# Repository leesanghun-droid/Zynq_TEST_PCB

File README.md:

Open kakao talk [LINK](https://open.kakao.com/o/gl8sklo)
# Zynq_TEST_PCB

Tool : kicad 6.0

  MAIN CHIP : XC7Z010-1CLG400C ([buy link](https://ko.aliexpress.com/item/4000052820744.html?gatewayAdapt=glo2kor&spm=a2g0o.order_list.0.0.21ef140fnMWK8L),  [metal mask buy link](https://ko.aliexpress.com/item/1005003821741873.html?gatewayAdapt=glo2kor&spm=a2g0o.order_list.0.0.21ef140fnMWK8L))

  DDR RAM CHIP : MT41K256M16HA-125( just usb form factor )

## Project step

### 1. make concept ( ~ 2022.04.05 )

      - 100Mbps ethernet
      - usb 2.0
      - ddr3 256MB 667Mhz
      - sd_card
      
### 2. drawing schematic ( ~ 2022.04.20 )

MAIN : XC7Z010-1CLG400C
POWER : ADP5052
JTAG : FT2232HQ
FLASH memory : 

4GB eMMC Flash
16MB QSPI Flash
TF card interface

DRAM : micron 4KK77-D9PTK
512MB DDR3 SDRAM (2 x 256MB, 32-bit)

DDR 고속 배선 아트웍 참조
https://m.blog.naver.com/PostView.naver?isHttpsRedirect=true&blogId=bestmind4276&logNo=220702125147

ethernet : RTL8211E
10/100/1000M Ethernet

usb host : USB3320C

아트웍 순서

1. DDR
2. EMMC
3. ETHERNET
4. USB
5. JTAG 
6. POWER

### 3. order pcb 

      - 4layer ( or 6layer )
      
### 4. hand Soldering

      - usb Metal Mask ( PCB Stencil )
      - HOT AIR FLOW GUN
      - FREE HEATTING BED
      
### 5. standard alone program test

### 6. linux poting

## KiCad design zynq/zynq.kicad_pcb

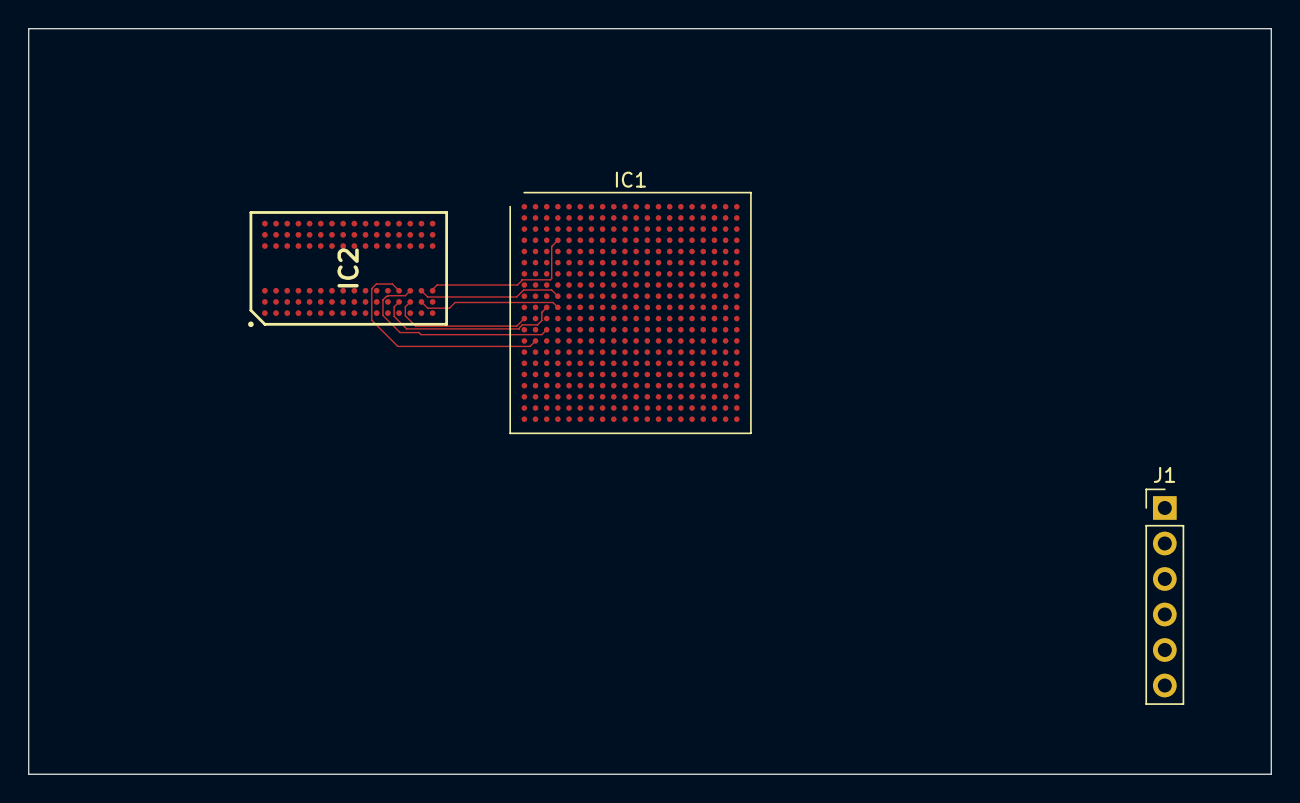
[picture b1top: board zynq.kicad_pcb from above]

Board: 6 copper layers, 88.9 x 53.3 mm, 3 parts (0 on the bottom side), 37 nets.

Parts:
IC1: Xilinx_CLG400
IC2: MT41J128M16JT-125_K; BGA96C80P9X16_800X1400X120
J1: POWER_SOURCE; PinHeader_1x06_P2.54mm_Vertical

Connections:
/CPU/DDR3_A0: IC1.N2 (PS_DDR_A0_502), IC2.N3 (A0)
/CPU/DDR3_A1: IC1.K2 (PS_DDR_A1_502), IC2.P7 (A1)
/CPU/DDR3_A2: IC1.M3 (PS_DDR_A2_502), IC2.P3 (A2)
/CPU/DDR3_A3: IC1.K3 (PS_DDR_A3_502), IC2.N2 (A3)
/CPU/DDR3_A4: IC1.M4 (PS_DDR_A4_502), IC2.P8 (A4)
/CPU/DDR3_A5: IC1.L1 (PS_DDR_A5_502), IC2.P2 (A5)
/CPU/DDR3_A6: IC1.L4 (PS_DDR_A6_502), IC2.R8 (A6)
/CPU/DDR3_A7: IC1.K4 (PS_DDR_A7_502), IC2.R2 (A7)
/CPU/DDR3_A8: IC1.K1 (PS_DDR_A8_502), IC2.T8 (A8)
/CPU/DDR3_A9: IC1.J4 (PS_DDR_A9_502), IC2.R3 (A9)
/CPU/DDR3_A10: IC1.F5 (PS_DDR_A10_502), IC2.L7 (A10/AP)
/CPU/DDR3_A11: IC1.G4 (PS_DDR_A11_502), IC2.R7 (A11)
/CPU/DDR3_A12: IC1.E4 (PS_DDR_A12_502), IC2.N7 (A12/BC#)
/CPU/DDR3_A13: IC1.D4 (PS_DDR_A13_502), IC2.T3 (A13)
/CPU/DDR3_A14: IC1.F4 (PS_DDR_A14_502), IC2.T7 (NC_6)
/CPU/DDR3_BA0: IC1.L5 (PS_DDR_BA0_502), IC2.M2 (BA0)
/CPU/DDR3_BA1: IC1.R4 (PS_DDR_BA1_502), IC2.N8 (BA1)
/CPU/DDR3_BA2: IC1.J5 (PS_DDR_BA2_502), IC2.M3 (BA2)
/CPU/DDR3_CKE0: IC1.N3 (PS_DDR_CKE_502), IC2.K9 (CKE)
/CPU/DDR3_CK_N: IC1.M2 (PS_DDR_CKN_502), IC2.K7 (CK#)
/CPU/DDR3_CK_P: IC1.L2 (PS_DDR_CKP_502), IC2.J7 (CK)
/CPU/DDR3_D0: IC1.E3 (PS_DDR_DQ9_502), IC2.E3 (DQ0)
/CPU/DDR3_D1: IC1.H2 (PS_DDR_DQ13_502), IC2.F7 (DQ1)
/CPU/DDR3_D2: IC1.E2 (PS_DDR_DQ8_502), IC2.F2 (DQ2)
/CPU/DDR3_D3: IC1.G3 (PS_DDR_DQ10_502), IC2.F8 (DQ3)
/CPU/DDR3_D4: IC1.J1 (PS_DDR_DQ15_502), IC2.H3 (DQ4)
/CPU/DDR3_D5: IC1.H3 (PS_DDR_DQ11_502), IC2.H8 (DQ5)
/CPU/DDR3_D6: IC1.J3 (PS_DDR_DQ12_502), IC2.G2 (DQ6)
/CPU/DDR3_D7: IC1.H1 (PS_DDR_DQ14_502), IC2.H7 (DQ7)
/CPU/DDR3_D8: IC1.D3 (PS_DDR_DQ4_502), IC2.D7 (DQ8)
/CPU/DDR3_D9: IC1.E1 (PS_DDR_DQ7_502), IC2.C3 (DQ9)
/CPU/DDR3_D10: IC1.C1 (PS_DDR_DQ6_502), IC2.C8 (DQ10)
/CPU/DDR3_D11: IC1.C3 (PS_DDR_DQ0_502), IC2.C2 (DQ11)
/CPU/DDR3_D12: IC1.B3 (PS_DDR_DQ1_502), IC2.A7 (DQ12)
/CPU/DDR3_D13: IC1.A2 (PS_DDR_DQ2_502), IC2.A2 (DQ13)
/CPU/DDR3_D14: IC1.D1 (PS_DDR_DQ5_502), IC2.B8 (DQ14)
/CPU/DDR3_D15: IC1.A4 (PS_DDR_DQ3_502), IC2.A3 (DQ15)

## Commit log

2022-04-23 Create PCB_ARTWORK_INFO
2022-04-23 Update PCB_ARTWORK_INFO
